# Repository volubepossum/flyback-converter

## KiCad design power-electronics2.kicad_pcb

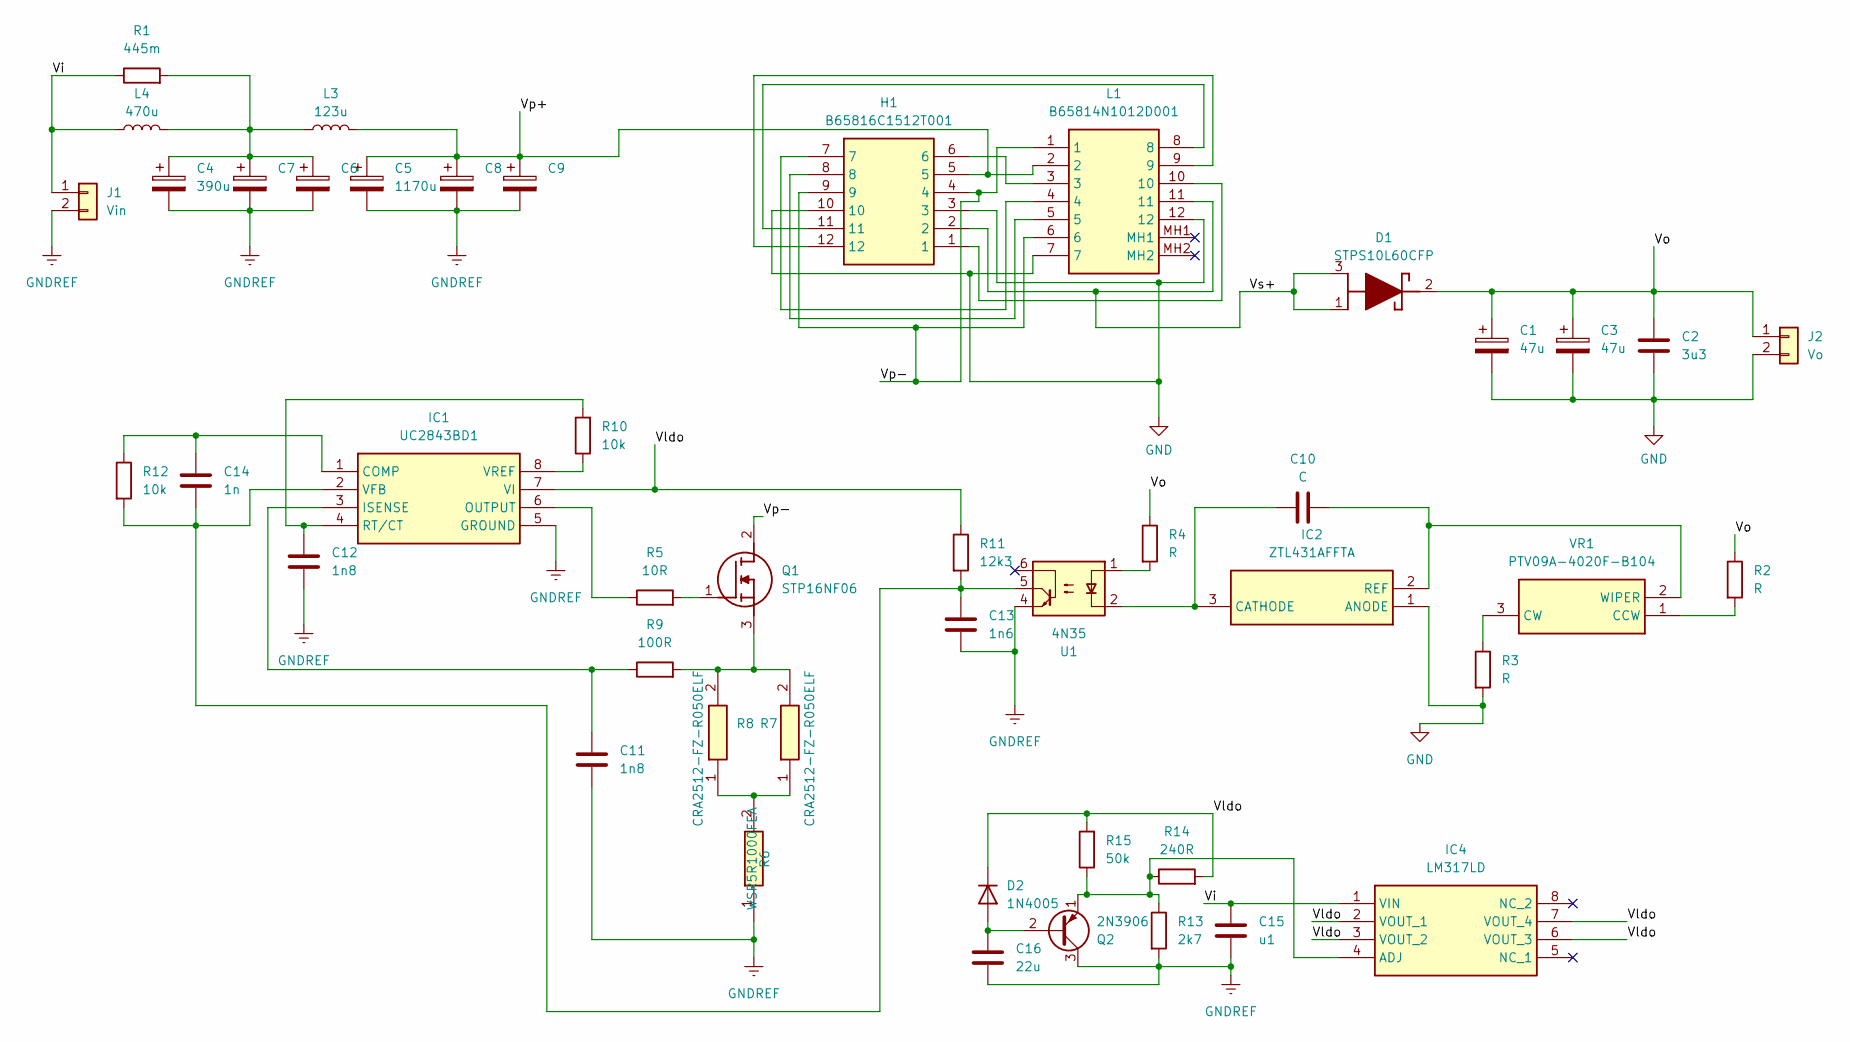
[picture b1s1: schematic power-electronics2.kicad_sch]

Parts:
C1, C3: 47u; CP_Radial_D10.0mm_P5.00mm
C2: 3u3; C_Axial_L12.0mm_D7.5mm_P15.00mm_Horizontal
C4: 390u; CP_Radial_D10.0mm_P5.00mm
C5: 1170u; CP_Radial_D16.0mm_P7.50mm
C6, C7, C8, C9: C; CP_Radial_D10.0mm_P5.00mm
C10: C; C_0805_2012Metric_Pad1.18x1.45mm_HandSolder
C11, C12: 1n8; C_0805_2012Metric_Pad1.18x1.45mm_HandSolder
C13: 1n6; C_0805_2012Metric_Pad1.18x1.45mm_HandSolder
C14: 1n; C_0805_2012Metric_Pad1.18x1.45mm_HandSolder
C15: u1; C_0805_2012Metric_Pad1.18x1.45mm_HandSolder
C16: 22u; C_0805_2012Metric_Pad1.18x1.45mm_HandSolder
D1: STPS10L60CFP; TO255P460X1020X2030-3P; Manufacturer_Part_Number STPS10L60CFP; Mouser Part Number 511-STPS10L60CFP
D2: 1N4005; D_DO-41_SOD81_P10.16mm_Horizontal
H1: B65816C1512T001; Manufacturer_Part_Number B65816C1512T001; Mouser Part Number 871-B65816C1512T1
IC1: UC2843BD1; SOIC127P600X175-8M; Manufacturer_Part_Number UC2843BD1; Mouser Part Number 511-UC2843BD1
IC2: ZTL431AFFTA; SOTFL95P240X110-3N; Manufacturer_Part_Number ZTL431AFFTA; Mouser Part Number 522-ZTL431AFFTA
IC4: LM317LD; SOIC127P600X175-8N; Manufacturer_Part_Number LM317LD; Mouser Part Number 511-LM317LD
J1: Vin; SolderWire-1.5sqmm_1x02_P6mm_D1.7mm_OD3mm
J2: Vo; SolderWire-1.5sqmm_1x02_P6mm_D1.7mm_OD3mm
L1: B65814N1012D001; Manufacturer_Part_Number B65814N1012D001; Mouser Part Number 871-B65814N1012D001
L3: 123u; L_Axial_L29.9mm_D14.0mm_P38.00mm_Horizontal_Vishay_IHA-105
L4: 470u; L_Axial_L29.9mm_D14.0mm_P38.00mm_Horizontal_Vishay_IHA-105
Q1: STP16NF06; TO270P460X1020X2008-3P; Manufacturer_Part_Number STP16NF06; Mouser Part Number 511-STP16NF06
Q2: 2N3906; TO-92_Inline
R1: 445m; R_0805_2012Metric_Pad1.20x1.40mm_HandSolder
R2, R3, R4: R; R_0805_2012Metric_Pad1.20x1.40mm_HandSolder
R5: 10R; R_0805_2012Metric_Pad1.20x1.40mm_HandSolder
R6: WSR5R1000FEA; RESM11670X254N; Manufacturer_Part_Number WSR5R1000FEA; Mouser Part Number 71-WSR5R1000FEA
R7, R8: CRA2512-FZ-R050ELF; RESC6434X90N; Manufacturer_Part_Number CRA2512-FZ-R050ELF; Mouser Part Number 652-CRA2512FZ-R50ELF
R9: 100R; R_0805_2012Metric_Pad1.20x1.40mm_HandSolder
R10, R12: 10k; R_0805_2012Metric_Pad1.20x1.40mm_HandSolder
R11: 12k3; R_0805_2012Metric_Pad1.20x1.40mm_HandSolder
R13: 2k7; R_0805_2012Metric_Pad1.20x1.40mm_HandSolder
R14: 240R; R_0805_2012Metric_Pad1.20x1.40mm_HandSolder
R15: 50k; R_0805_2012Metric_Pad1.20x1.40mm_HandSolder
U1: 4N35; DIP-6_W7.62mm_SMDSocket_SmallPads
VR1: PTV09A-4020F-B104; PTV09A4020FB103; Manufacturer_Part_Number PTV09A-4020F-B104; Mouser Part Number 652-PTV09A-4020FB104

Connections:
/Vi: C15.1, IC4.1 (VIN), J1.1, L4.1, R1.1
/Vldo: D2.1 (K), IC1.7 (VI), IC4.2 (VOUT_1), IC4.3 (VOUT_2), IC4.6 (VOUT_3), IC4.7 (VOUT_4), R11.1, R14.2, R15.2
/Vo: C1.1, C2.1, C3.1, D1.2 (K), J2.1, R2.1, R4.1
/Vp+: C5.1, C8.1, C9.1, H1.5, L1.2, L3.2
/Vp-: H1.4, H1.9, L1.1, L1.6, Q1.2 (D)
/Vs+: D1.1 (A1), D1.3 (A2), H1.2, L1.11
GND: C1.2, C2.2, C3.2, H1.3, H1.10, IC2.1 (ANODE), J2.2, L1.7, L1.12, R3.2
GNDREF: C4.2, C5.2, C6.2, C7.2, C8.2, C9.2, C11.2, C12.2, C13.2, C15.2, C16.2, IC1.5 (GROUND), J1.2, Q2.3 (C), R6.1, R13.2, U1.4
unnamed: C4.1, C6.1, C7.1, L3.1, L4.2, R1.2
unnamed: C16.1, D2.2 (A), Q2.2 (B)
unnamed: H1.1, L1.10
unnamed: H1.6, L1.3
unnamed: H1.7, L1.4
unnamed: H1.8, L1.5
unnamed: H1.11, L1.8
unnamed: H1.12, L1.9
unnamed: C14.1, IC1.1 (COMP), R12.1
unnamed: C11.1, IC1.3 (ISENSE), R9.1
unnamed: IC1.6 (OUTPUT), R5.1
unnamed: C12.1, IC1.4 (RT/CT), R10.2
unnamed: C13.1, C14.2, IC1.2 (VFB), R11.2, R12.2, U1.5
unnamed: IC1.8 (VREF), R10.1
unnamed: C10.1, IC2.3 (CATHODE), U1.2
unnamed: C10.2, IC2.2 (REF), VR1.2 (WIPER)
unnamed: IC4.4 (ADJ), Q2.1 (E), R13.1, R14.1, R15.1
unnamed: Q1.1 (G), R5.2
unnamed: Q1.3 (S), R7.2, R8.2, R9.2
unnamed: R4.2, U1.1
unnamed: R6.2, R7.1, R8.1
unnamed: R2.2, VR1.1 (CCW)
unnamed: R3.1, VR1.3 (CW)

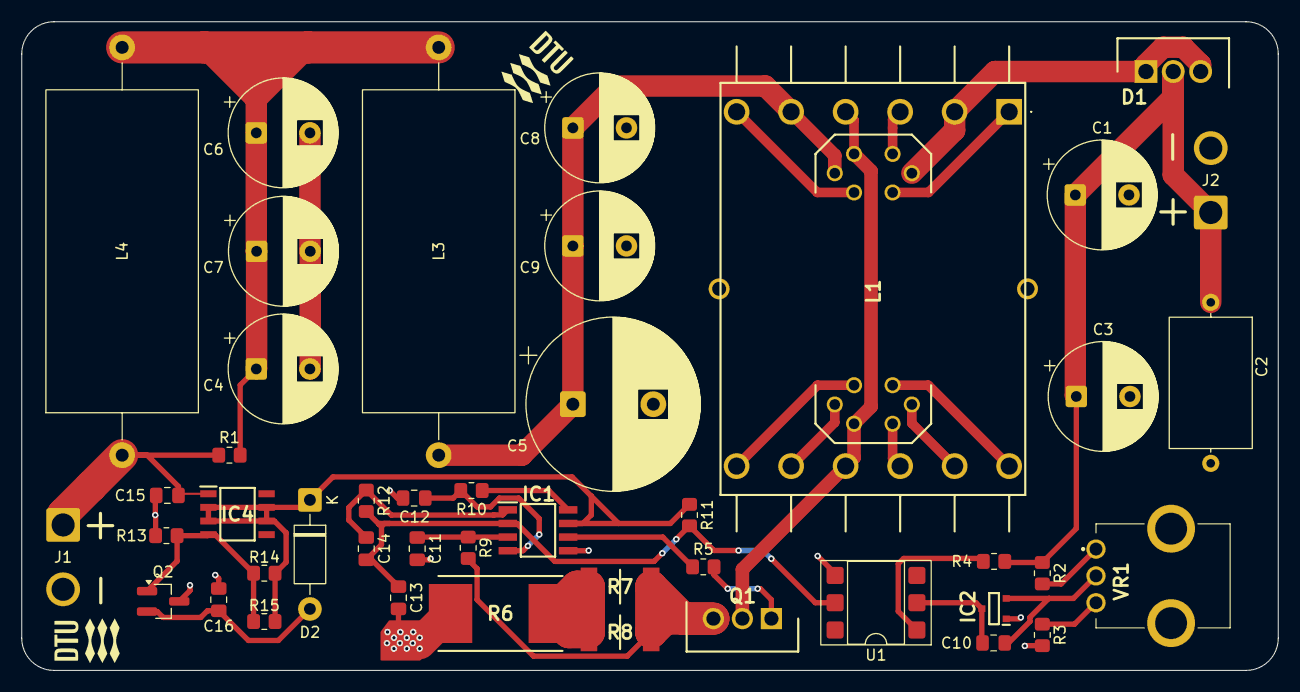
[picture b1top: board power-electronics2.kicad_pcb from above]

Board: 2 copper layers, 117.1 x 60.5 mm, 46 parts (0 on the bottom side), 31 nets.

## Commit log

2026-01-04 init
2026-01-04 Add .gitignore
2026-01-04 remove gitignore files
2026-01-04 add schematics and footprints to project
2026-01-04 add some components
2026-01-05 add components
2026-01-07 finish pcb
2026-01-07 finishing touches & gerber
